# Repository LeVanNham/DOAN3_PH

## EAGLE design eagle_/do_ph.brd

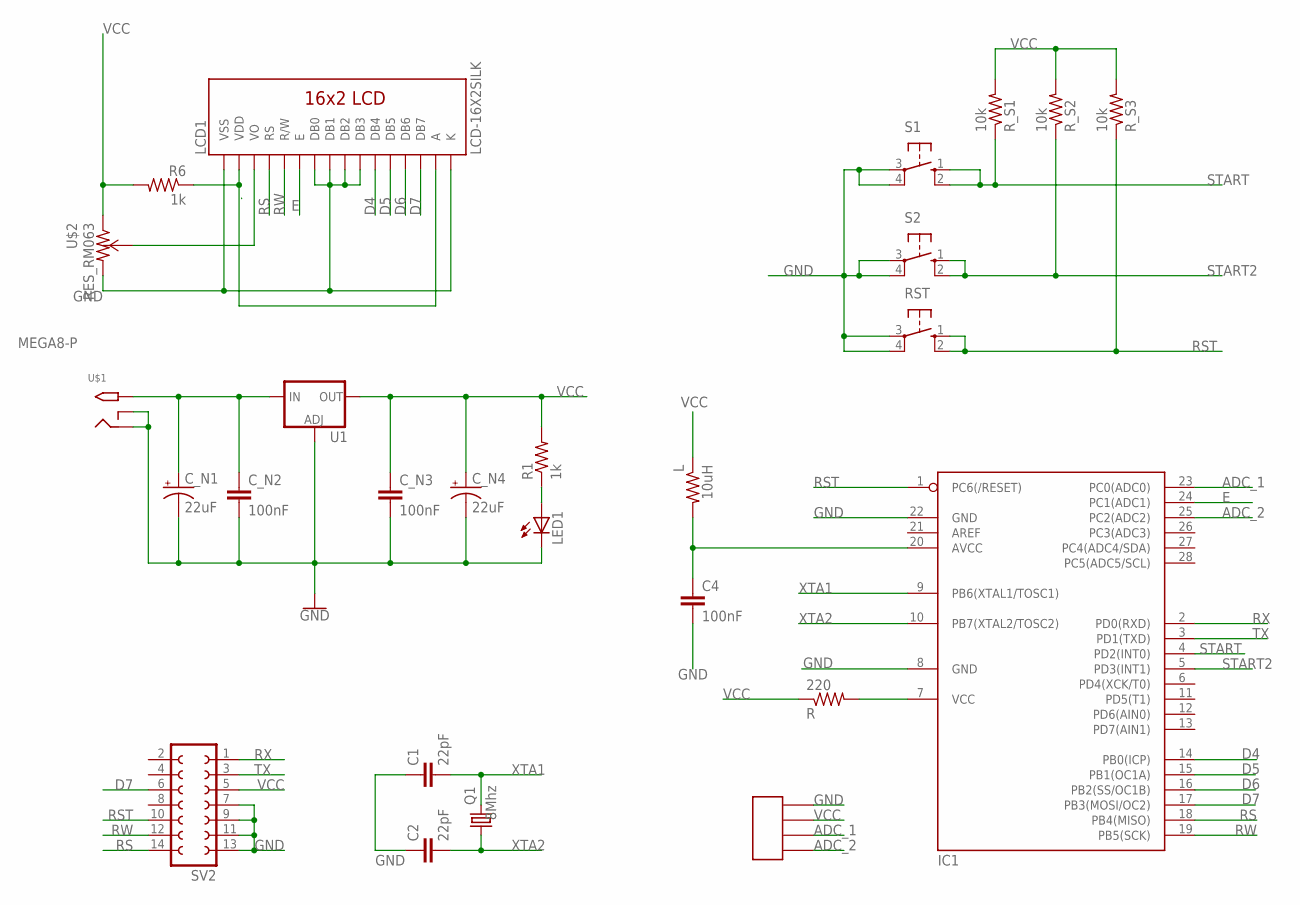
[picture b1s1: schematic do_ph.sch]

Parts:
C1, C2: 22pF; 0402-CAP
C4: 100nF; 0805
C_N1, C_N4: 22uF; CT7343
C_N2, C_N3: 100nF; 0805
IC1: MEGA8-P; DIL28-3
L: 10uH; R0805
LCD1: LCD-16X2SILK; LCD-16X2
LED1: LED_E; LED_1206
Q1: 8Mhz; HC49/S
R: 220; R0805
R1, R6: 1k; R0805
RST: 10-XX; B3F-10XX
R_S1, R_S2, R_S3: 10k; R0805
S1, S2: 10-XX; B3F-10XX
SV2: FE07-2
U1: V_REG_LM1117SOT223; SOT223
U$1: 2.1MMJACK; PJ-102A
U$2: RES_RM063; RM063
U$5: PH_SENSOR_DFROBOT; PH_DFROBOT

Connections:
ADC_1: IC1.23 (PC0(ADC0)), U$5.S_A (P_A)
ADC_2: IC1.25 (PC2(ADC2)), U$5.S_A2 (P_A2)
D4: IC1.14 (PB0(ICP)), LCD1.11 (DB4)
D5: IC1.15 (PB1(OC1A)), LCD1.12 (DB5)
D6: IC1.16 (PB2(SS/OC1B)), LCD1.13 (DB6)
D7: IC1.17 (PB3(MOSI/OC2)), LCD1.14 (DB7), SV2.6
E: IC1.24 (PC1(ADC1)), LCD1.6 (E)
GND: C1.1, C2.1, C4.2, C_N1.-, C_N2.2, C_N3.2, C_N4.-, IC1.8 (GND), IC1.22 (GND), LCD1.1 (VSS), LCD1.7 (DB0), LCD1.8 (DB1), LCD1.9 (DB2), LCD1.10 (DB3), LCD1.16 (K), LED1.C, RST.3, RST.4 (P1), S1.3, S1.4 (P1), S2.3, S2.4 (P1), SV2.7, SV2.9, SV2.11, SV2.13, U1.1 (ADJ), U$1.RING, U$1.RING_SW, U$2.P$2, U$5.S_GND (P_GND)
unnamed: LCD1.3 (VO), U$2.P$3
unnamed: C_N1.+, C_N2.1, U1.3 (IN), U$1.TIP
unnamed: LED1.A, R1.1
unnamed: C4.1, IC1.20 (AVCC), L.2
unnamed: IC1.7 (VCC), R.2
RS: IC1.18 (PB4(MISO)), LCD1.4 (RS), SV2.14
RST: IC1.1 (PC6(/RESET)), RST.1 (S), RST.2 (S1), R_S3.1, SV2.10
RW: IC1.19 (PB5(SCK)), LCD1.5 (R/W), SV2.12
RX: IC1.2 (PD0(RXD)), SV2.1
START: IC1.4 (PD2(INT0)), R_S1.1, S1.1 (S), S1.2 (S1)
START2: IC1.5 (PD3(INT1)), R_S2.1, S2.1 (S), S2.2 (S1)
TX: IC1.3 (PD1(TXD)), SV2.3
VCC: C_N3.1, C_N4.+, L.1, R.1, R1.2, R6.2, R_S1.2, R_S2.2, R_S3.2, SV2.5, U1.2 (OUT), U1.4 (OUT), U$2.P$1, U$5.S_VCC (P_VCC)
VO: LCD1.2 (VDD), LCD1.15 (A), R6.1
XTA1: C1.2, IC1.9 (PB6(XTAL1/TOSC1)), Q1.2
XTA2: C2.2, IC1.10 (PB7(XTAL2/TOSC2)), Q1.1

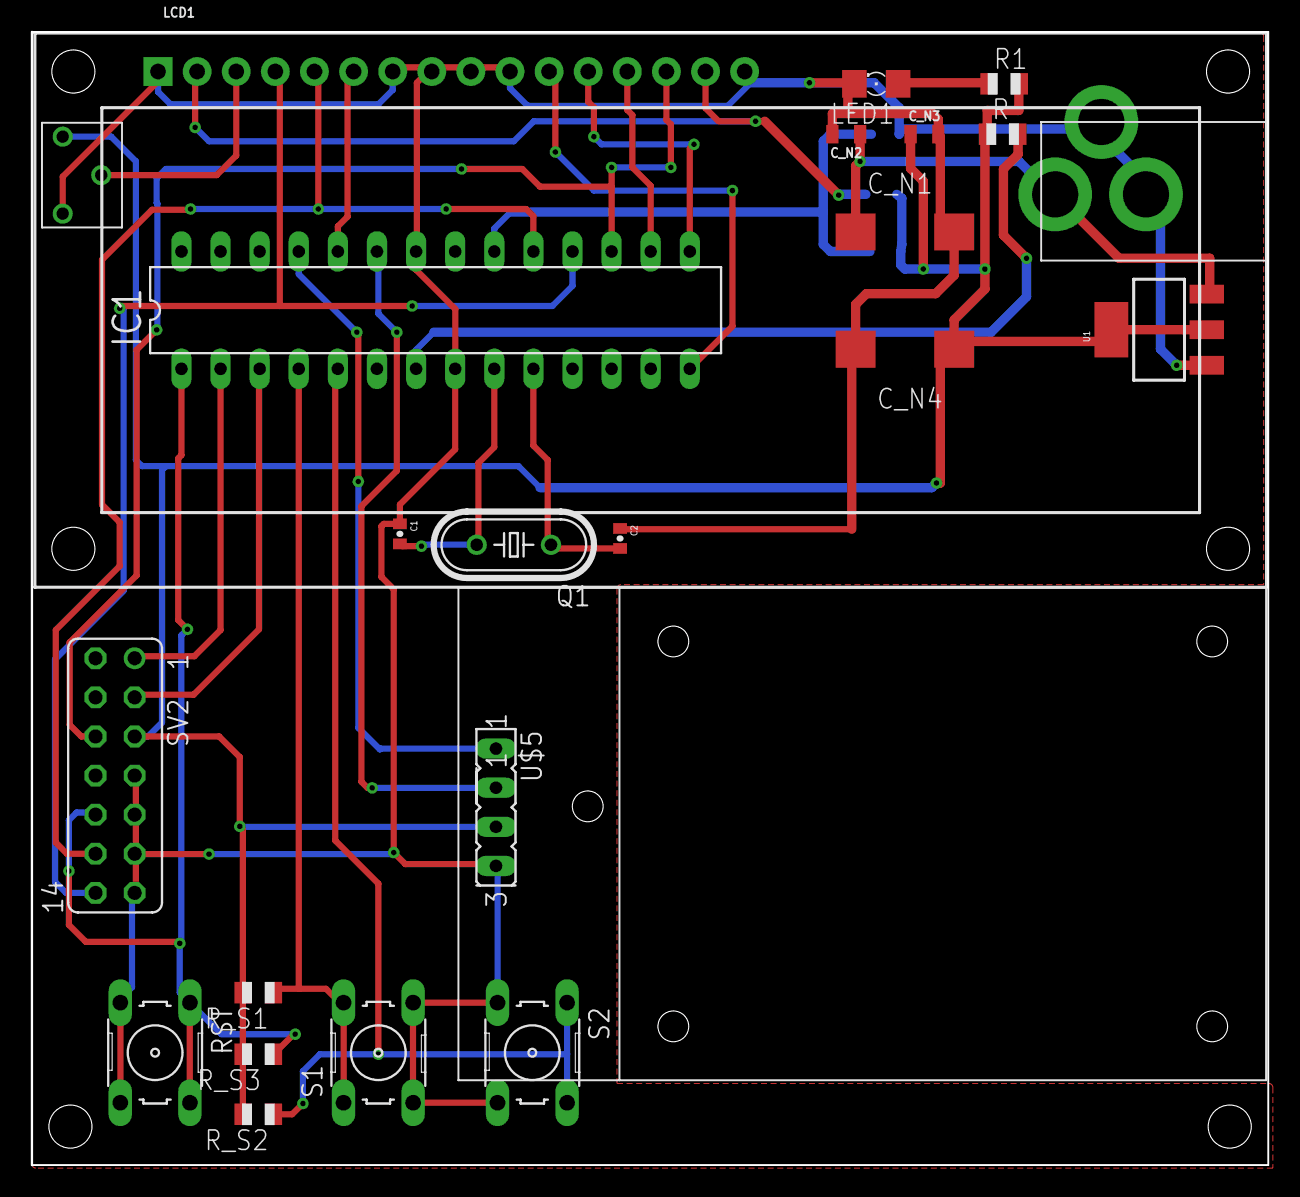
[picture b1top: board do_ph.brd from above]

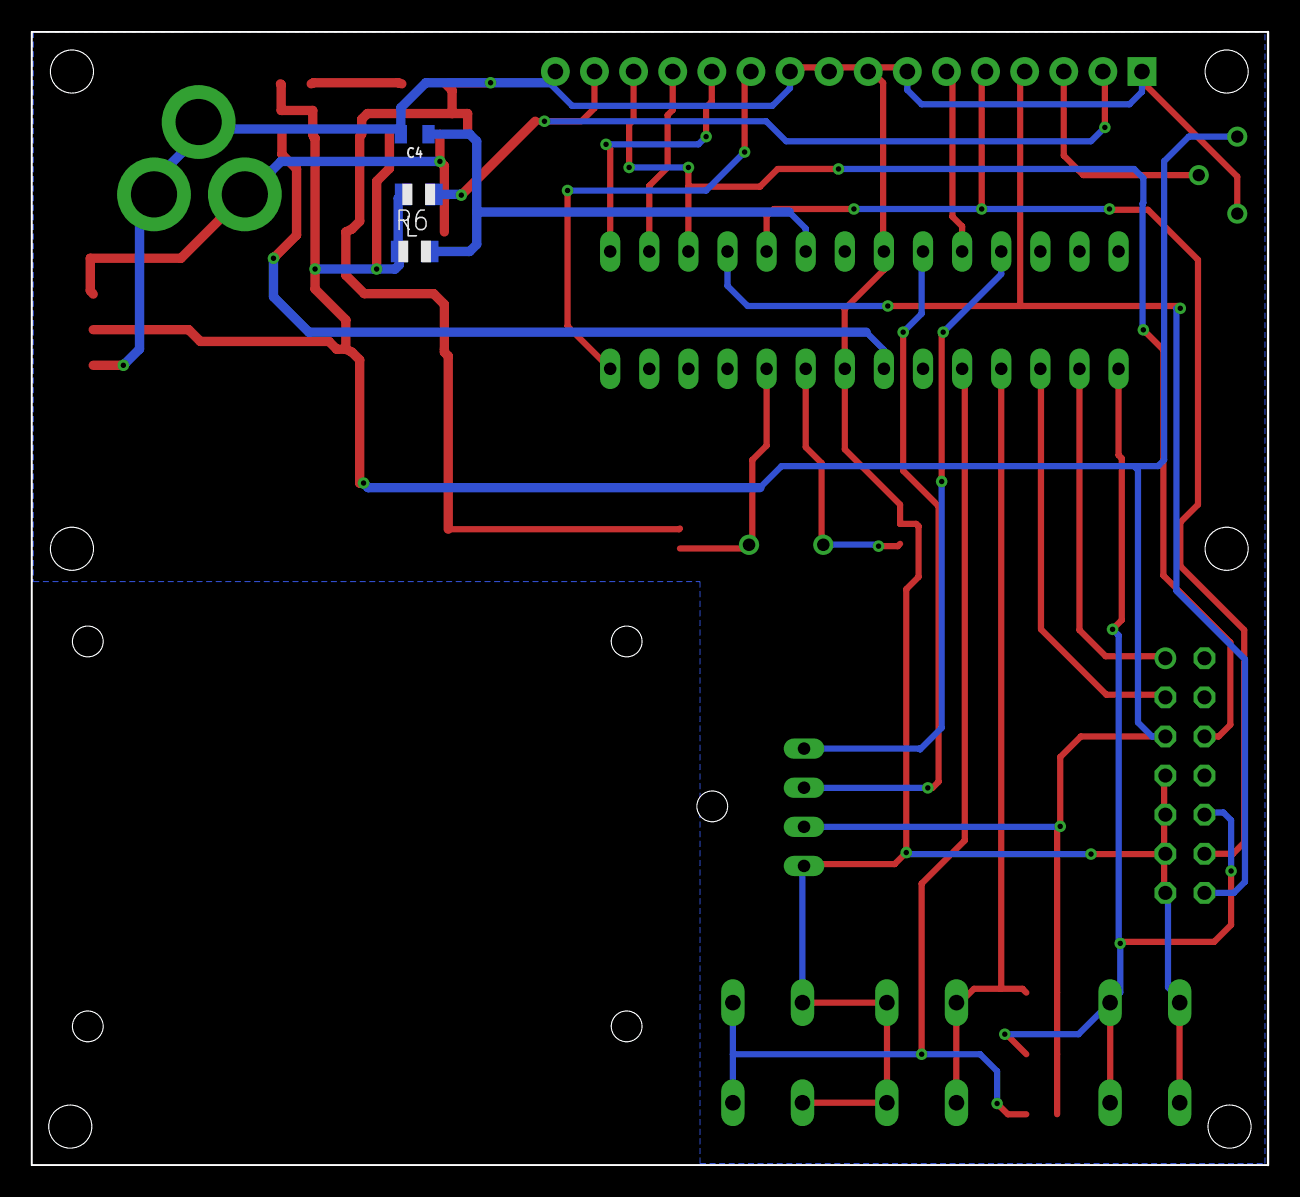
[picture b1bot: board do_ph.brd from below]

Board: 2 copper layers, 80.3 x 73.6 mm, 26 parts (3 on the bottom side), 24 nets.

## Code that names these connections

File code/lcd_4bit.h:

#include <util/delay.h>

#define PORT_LCD PORTB
#define DDR_LCD DDRB

#define PORT_CTRL_LCD PORTB
#define DDR_CTRL_LCD DDRB

#define sbi(port,bit) port|=_BV(bit)
#define cbi(port,bit) port&=~_BV(bit)

#define RS PB4
#define RW PB5
#define EN PC1


#define D4 PB0
#define D5 PB1
#define D6 PB2
#define D7 PB3

#define time_ms 15
#define time_us 400

#define RS_HIGH sbi(PORT_CTRL_LCD,RS)
#define RW_HIGH sbi(PORT_CTRL_LCD,RW)
#define EN_HIGH sbi(PORTC,EN)

#define RS_LOW cbi(PORT_CTRL_LCD,RS)
#define RW_LOW cbi(PORT_CTRL_LCD,RW)
#define EN_LOW cbi(PORTC,EN)

#define lcd_wait1 _delay_ms(15)
#define lcd_wait2 _delay_us(400)

#define lcd_out_4bit(data) {PORT_LCD &=0xf0;PORT_LCD|=(data&0x0f);EN_HIGH;lcd_wait1;EN_LOW;lcd_wait2;}

#define lcd_send(data) {lcd_out_4bit(data>>4);lcd_out_4bit(data);}
//#define lcd_send(data) { PORT_LCD=data; EN_HIGH; _delay_ms(time_ms); EN_LOW;}
#define lcd_putChar(chr) { RS_HIGH,RW_LOW; lcd_send(chr); _delay_us(time_us);}
#define lcd_cmd(cmd) { RS_LOW; RW_LOW; lcd_send(cmd); _delay_us(time_us);}
#define lcd_move(y,x) lcd_cmd(0x80 + 0x40*(y-1) + x-1)
#define lcd_clear lcd_cmd(0x01);




void lcd_putString(char *s){
	while(*s){
		lcd_putChar(*s);
		s++;
	}
}

void lcd_print_number(double n){
   uint16_t a,b,i,x;
   char num[10];
   a=n;
   b=(n-a)*1000+1000;
   i=9;
   
   while(b){
      x=b%10;
      b=b/10;
      num[i]=x+48;
      i--;
   }
   i++;
   num[i]='.';
   i--;
   if(a==0) {num[i]='0'; i--;}
   else while (a){
      x=a%10;
      a=a/10;
      num[i]=x+48;
      i--;
   }
   
   i++;
   while(i<10){
      //++i;
      lcd_putChar(num[i]);
      i++;
      }
   
}

void lcd_init(){
       DDR_LCD|=0x3F;
       DDRC|=0x02;
   
	RS_LOW;
	RW_LOW;
	_delay_us(time_us);

	lcd_send(0x03);
	_delay_us(time_us);
	
	lcd_send(0x02);
	_delay_us(time_us);

	lcd_send(0x28);
	_delay_us(time_us);

	lcd_send(0x01);
	_delay_us(time_us);

	lcd_send(0x0f);
	_delay_us(time_us);

	lcd_send(0x06);
	_delay_us(time_us);

	lcd_send(0x0c);
	_delay_us(time_us);
}

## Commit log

2019-03-15 cap nhat
2019-03-18 thêm jack nap code
2019-04-05 update mạch in

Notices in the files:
parts and their libraries:
SparkFun-Capacitors: Licensing: Creative Commons ShareAlike 4.0 International - https://creativecommons.org/licenses/by-sa/4.0
